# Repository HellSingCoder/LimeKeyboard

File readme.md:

# Lime Keyboard

Lime is a 6×4+6 keys column-staggered split keyboard with encoder and joystick support. Based on [Lily58](https://github.com/kata0510/Lily58), [Corne](https://github.com/foostan/crkbd), [Helix](https://github.com/MakotoKurauchi/helix) and [Sofle](https://github.com/josefadamcik/SofleKeyboard) keyboards. This board features a reversible PCB, OLEDs, Underglow and Bluetooth support. The PCB has holes for floating or screwed mounts but can be also mounted with a gasket.

The Lime keyboard was created by [HellTM](https://github.com/HellSingCoder) with the help of the QMK and custom keyboard community.

**If you would like one of these contact me, I will probably run a couple batches in the future.**

## Firmware 

This keyboard runs [QMK](https://qmk.fm/) (no VIA support).

## Default layout 

### Base layer

The layout can be switched for COLEMAK in the settings layer

### Lower layer

### Raise layer

### Settings layer

This layer can be accessed with the following combination:

## Extras

### Keyboard Pet (Luna)

Luna jumps every time you hit Space and will bark at people on the internet if you activate Caps Lock!

This keyboard pet reacts to your WPM counter:
- under 10 -> sit
- between 10 and 50 -> walk
- over 50 -> run

### Shift + Backspace = Delete
This one is pretty self explanatory.

### Space / Enter swap
The Enter and Space functions can be swapped pressing the left thumb button from the Setting layer. The current mode will be displayed on the left display. This one may be useful to all the gamers out there!

### OS Switch
Pressing the OS button while on the settings layer will toggle the MAC / WIN mode. This corrects the behaviour of the Alt and Control modifiers. The current selection will be displayed with an icon at the top of the left display.

### Media Buttons
The right encoder controls the volume and can be pressed to mute. Extra media buttons are hidden away on the settings layer.

### RGB Underglow Support
The board features a 5 LEDs extensible or overridable underglow. Unfortunately, the default keymap does not take advantage of that because of the very limited space but, the option is out there if you want to play around with it.

### WPM indicator
Current WPM will be displayed at the bottom of the right screen.

### Joystick Debug
The JDebug button on the settings layer toggles the ADC readings of the joystick pins for X and Y axis. These will be displayed on the left OLED.

## Special thanks

[Envious](https://github.com/Envious-Data) - Kicad sage

[Dasky](https://github.com/daskygit) - Joystick Troubleshooting guru

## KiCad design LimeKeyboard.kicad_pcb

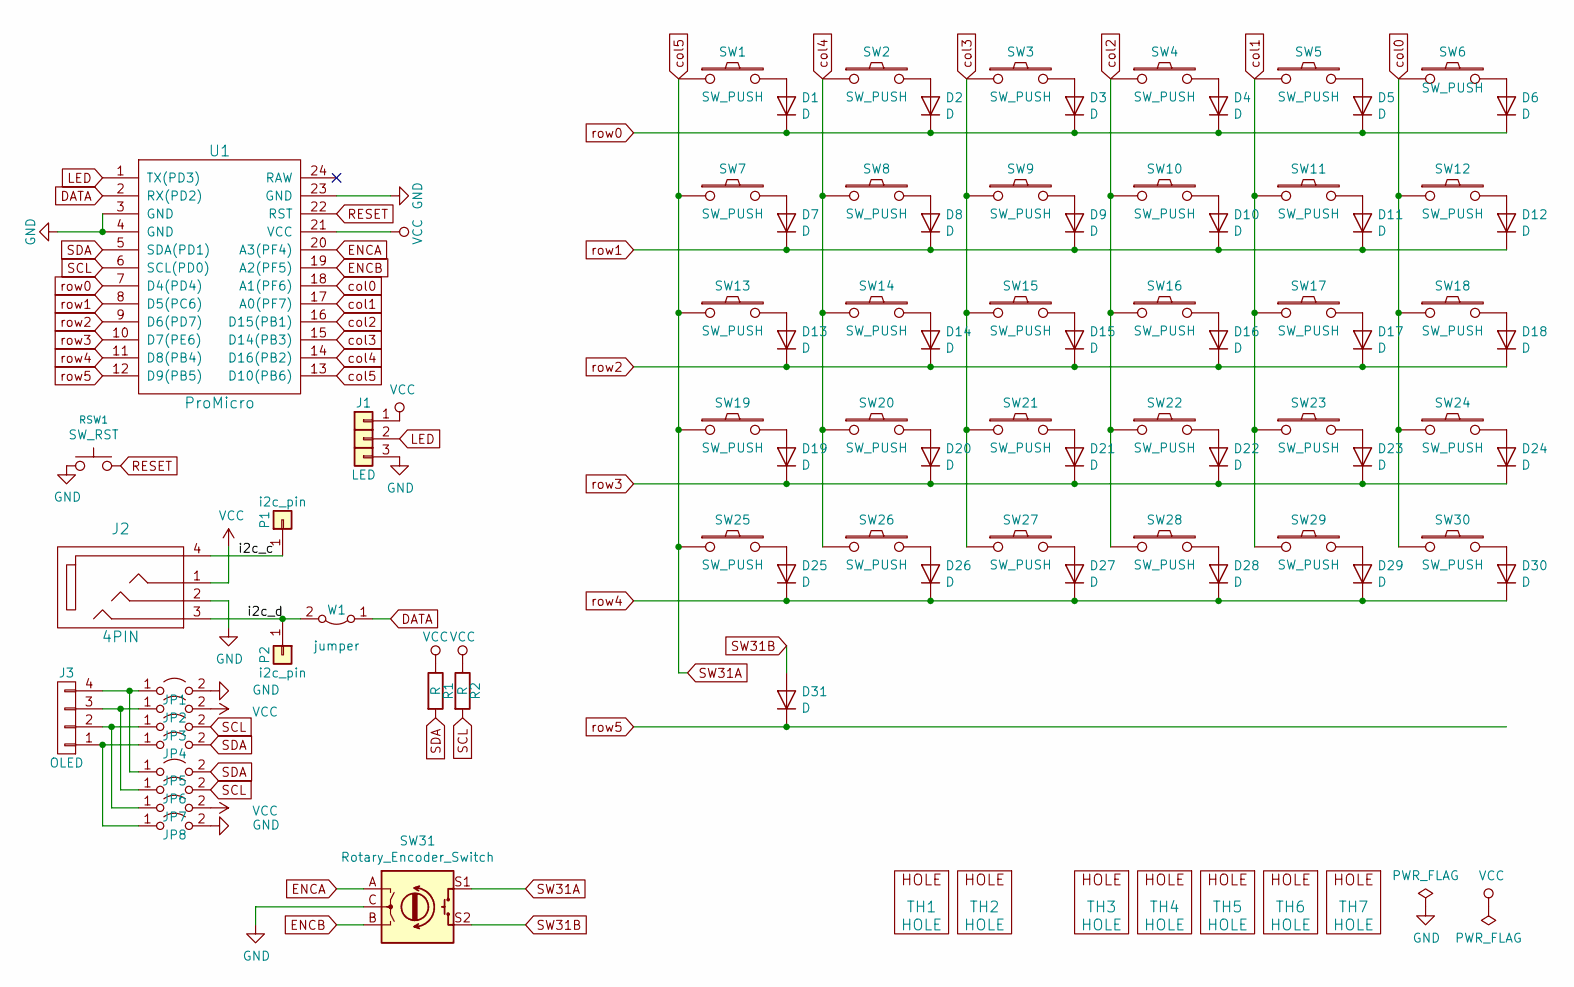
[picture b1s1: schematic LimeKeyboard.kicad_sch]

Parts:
D1, D2, D3, D4, D5, D6, D7, D8, D9, D10, D11, D12, D13, D14, D15, D16, D17, D18, D19, D20, D21, D22, D23, D24, D25, D26, D27, D28, D29, D30, D31: D; Diode_SOD123
J1: LED
J2: 4PIN; MJ-4PP-9
J3: OLED; OLED_4Pin
JP1, JP2, JP3, JP4, JP5, JP6, JP7, JP8: Jumper_NO_Small; Jumper
P1, P2: i2c_pin; 1pin_conn
R1, R2: R; RESISTOR_mini
RSW1: SW_RST; TACT_SWITCH_TVBP06
SW1, SW2, SW3, SW4, SW5, SW6, SW7, SW8, SW9, SW10, SW11, SW12, SW13, SW14, SW15, SW16, SW17, SW18, SW19, SW20, SW21, SW22, SW23, SW24, SW27, SW28, SW29, SW30: SW_PUSH; CherryMX_KailhLowProfile_Hotswap
SW25, SW26: SW_PUSH; CherryMX_KailhLowProfile_Hotswap_1.5
SW31: Rotary_Encoder_Switch; RotaryEncoder_Alps_EC11E-Switch_Vertical_H20mm-keebio_modif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
TH1, TH2: HOLE; M2_HOLE_PCB
TH3, TH4, TH5, TH6, TH7: HOLE; HOLE_M2_TH
U1: ProMicro
W1: jumper; jumper_data

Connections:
/i2c_c: J2.4, P1.1
/i2c_d: J2.3, P2.1, W1.2 (B)
DATA: U1.2 (RX(PD2)), W1.1 (A)
ENCA: SW31.A, U1.20 (A3(PF4))
ENCB: SW31.B, U1.19 (A2(PF5))
GND: J1.3, J2.2, JP1.2 (B), JP8.2 (B), RSW1.1, SW31.C, U1.3 (GND), U1.4 (GND), U1.23 (GND)
LED: J1.2, U1.1 (TX(PD3))
unnamed: D1.2 (A), SW1.2
unnamed: D2.2 (A), SW2.2
unnamed: D3.2 (A), SW3.2
unnamed: D4.2 (A), SW4.2
unnamed: D5.2 (A), SW5.2
unnamed: D6.2 (A), SW6.2
unnamed: D7.2 (A), SW7.2
unnamed: D8.2 (A), SW8.2
unnamed: D9.2 (A), SW9.2
unnamed: D10.2 (A), SW10.2
unnamed: D11.2 (A), SW11.2
unnamed: D12.2 (A), SW12.2
unnamed: D13.2 (A), SW13.2
unnamed: D14.2 (A), SW14.2
unnamed: D15.2 (A), SW15.2
unnamed: D16.2 (A), SW16.2
unnamed: D17.2 (A), SW17.2
unnamed: D18.2 (A), SW18.2
unnamed: D19.2 (A), SW19.2
unnamed: D20.2 (A), SW20.2
unnamed: D21.2 (A), SW21.2
unnamed: D22.2 (A), SW22.2
unnamed: D23.2 (A), SW23.2
unnamed: D24.2 (A), SW24.2
unnamed: D25.2 (A), SW25.2
unnamed: D26.2 (A), SW26.2
unnamed: D27.2 (A), SW27.2
unnamed: D28.2 (A), SW28.2
unnamed: D29.2 (A), SW29.2
unnamed: D30.2 (A), SW30.2
unnamed: J3.1, JP4.1 (A), JP8.1 (A)
unnamed: J3.2, JP3.1 (A), JP7.1 (A)
unnamed 39: J3.3, JP2.1 (A), JP6.1 (A); also elsewhere on the board
unnamed: J3.4, JP1.1 (A), JP5.1 (A)
RESET: RSW1.2, U1.22 (RST)
SCL: JP3.2 (B), JP6.2 (B), R2.2, U1.6 (SCL(PD0)); also elsewhere on the board
SDA: JP4.2 (B), JP5.2 (B), R1.2, U1.5 (SDA(PD1))
SW31A: SW1.1, SW7.1, SW13.1, SW19.1, SW25.1, SW31.S1, U1.13 (D10(PB6))
SW31B: D31.2 (A), SW31.S2
VCC: J1.1, J2.1, JP2.2 (B), JP7.2 (B), R1.1, R2.1, U1.21 (VCC)
col0: SW6.1, SW12.1, SW18.1, SW24.1, SW30.1, U1.18 (A1(PF6))
col1: SW5.1, SW11.1, SW17.1, SW23.1, SW29.1, U1.17 (A0(PF7))
col2: SW4.1, SW10.1, SW16.1, SW22.1, SW28.1, U1.16 (D15(PB1))
col3: SW3.1, SW9.1, SW15.1, SW21.1, SW27.1, U1.15 (D14(PB3))
col4: SW2.1, SW8.1, SW14.1, SW20.1, SW26.1, U1.14 (D16(PB2))
row0: D1.1 (K), D2.1 (K), D3.1 (K), D4.1 (K), D5.1 (K), D6.1 (K), U1.7 (D4(PD4))
row1: D7.1 (K), D8.1 (K), D9.1 (K), D10.1 (K), D11.1 (K), D12.1 (K), U1.8 (D5(PC6))
row2: D13.1 (K), D14.1 (K), D15.1 (K), D16.1 (K), D17.1 (K), D18.1 (K), U1.9 (D6(PD7))
row3: D19.1 (K), D20.1 (K), D21.1 (K), D22.1 (K), D23.1 (K), D24.1 (K), U1.10 (D7(PE6))
row4: D25.1 (K), D26.1 (K), D27.1 (K), D28.1 (K), D29.1 (K), D30.1 (K), U1.11 (D8(PB4))
row5: D31.1 (K), U1.12 (D9(PB5))

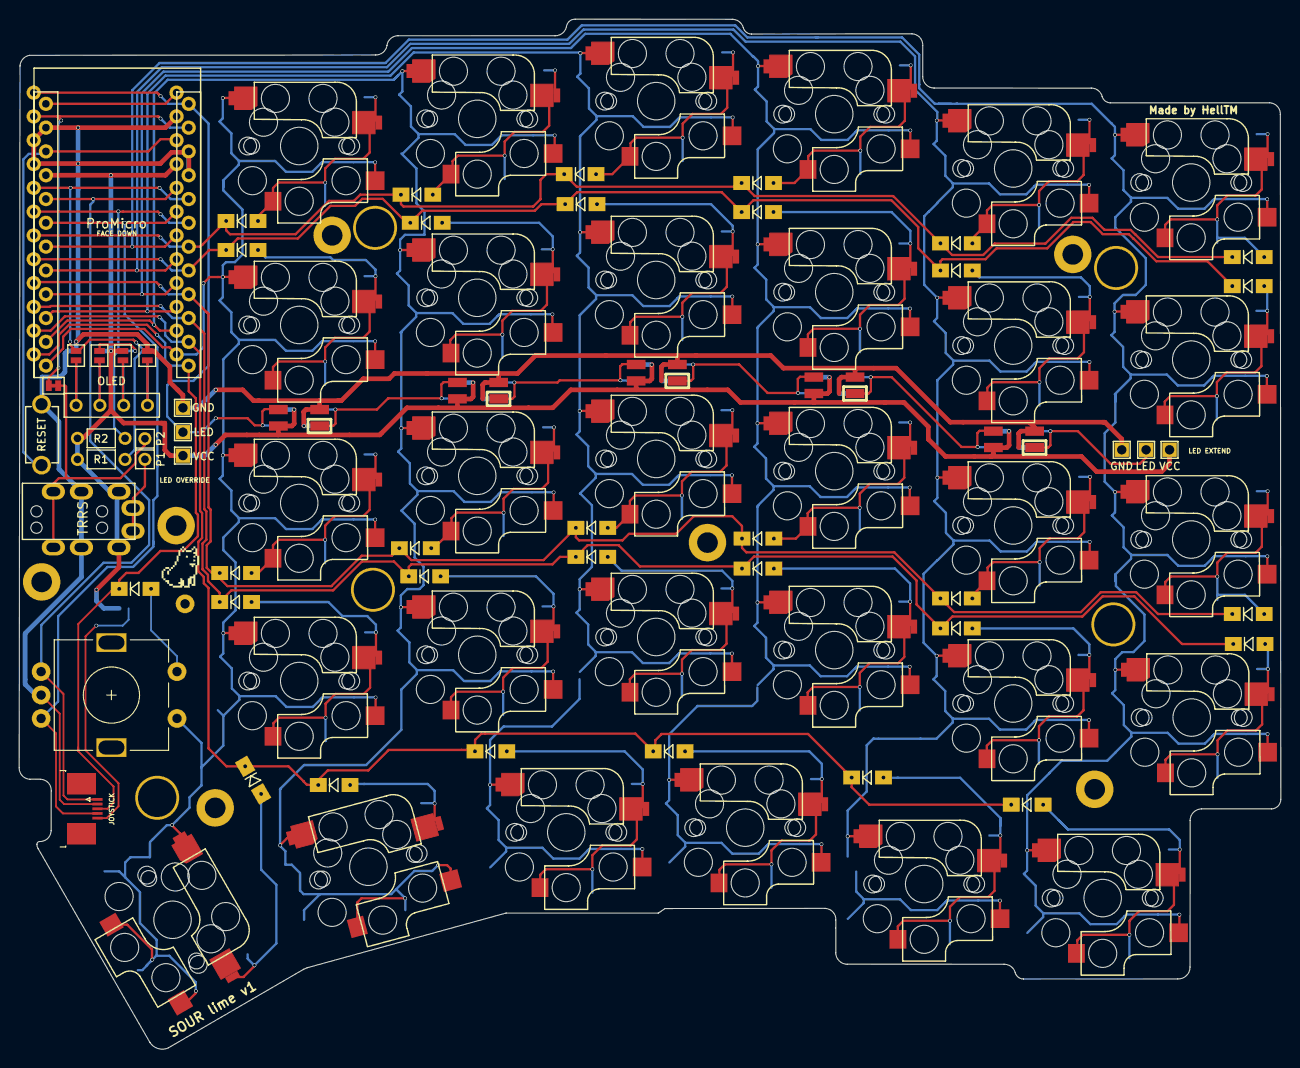
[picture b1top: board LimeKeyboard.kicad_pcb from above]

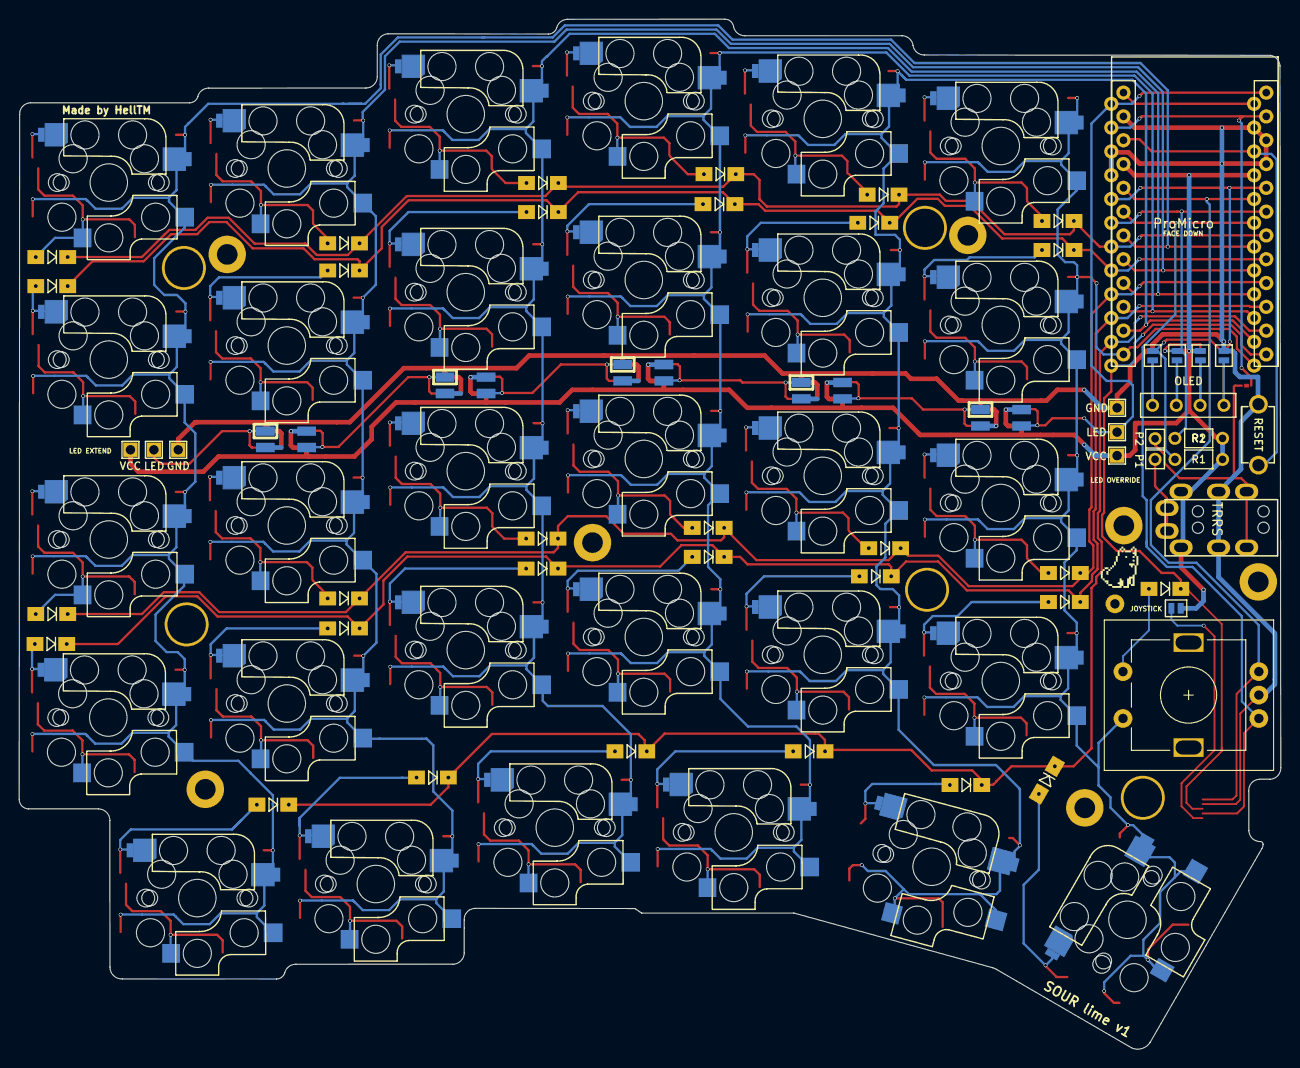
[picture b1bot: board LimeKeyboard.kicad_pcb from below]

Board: 2 copper layers, 134.6 x 109.9 mm, 102 parts (6 on the bottom side), 57 nets.

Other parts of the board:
D32, D33, D34, D35, D36: LED_sk2812_SM; SK6812MINI_underglow_dev
JOYSTICK: PCB Edge; TE_0-1734839-5_1x05-1MP_P0.5mm_Horizontal
JP6#2: Jumper_NO_Small; Jumper
LED: LED
LED#2: LED
LOGO: Luna
LOGO#2: Luna
TH3#2, TH4#2, TH6#2, TH7#2: HOLE; HOLE_M2_TH
TH5#2: HOLE; M2_HOLE_PCB

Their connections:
unnamed 39: JP6#2.1 (A); also elsewhere on the board
SCL: JP6#2.2 (B); also elsewhere on the board

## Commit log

2021-08-06 slim case
2021-09-25 new version
2021-09-25 added pcb stl
2021-09-25 made sure things are all local to this project
2021-10-05 readme
2021-10-05 license
2021-10-05 fixed typo
2021-10-05 folders cleanup
2021-11-21 new case files
